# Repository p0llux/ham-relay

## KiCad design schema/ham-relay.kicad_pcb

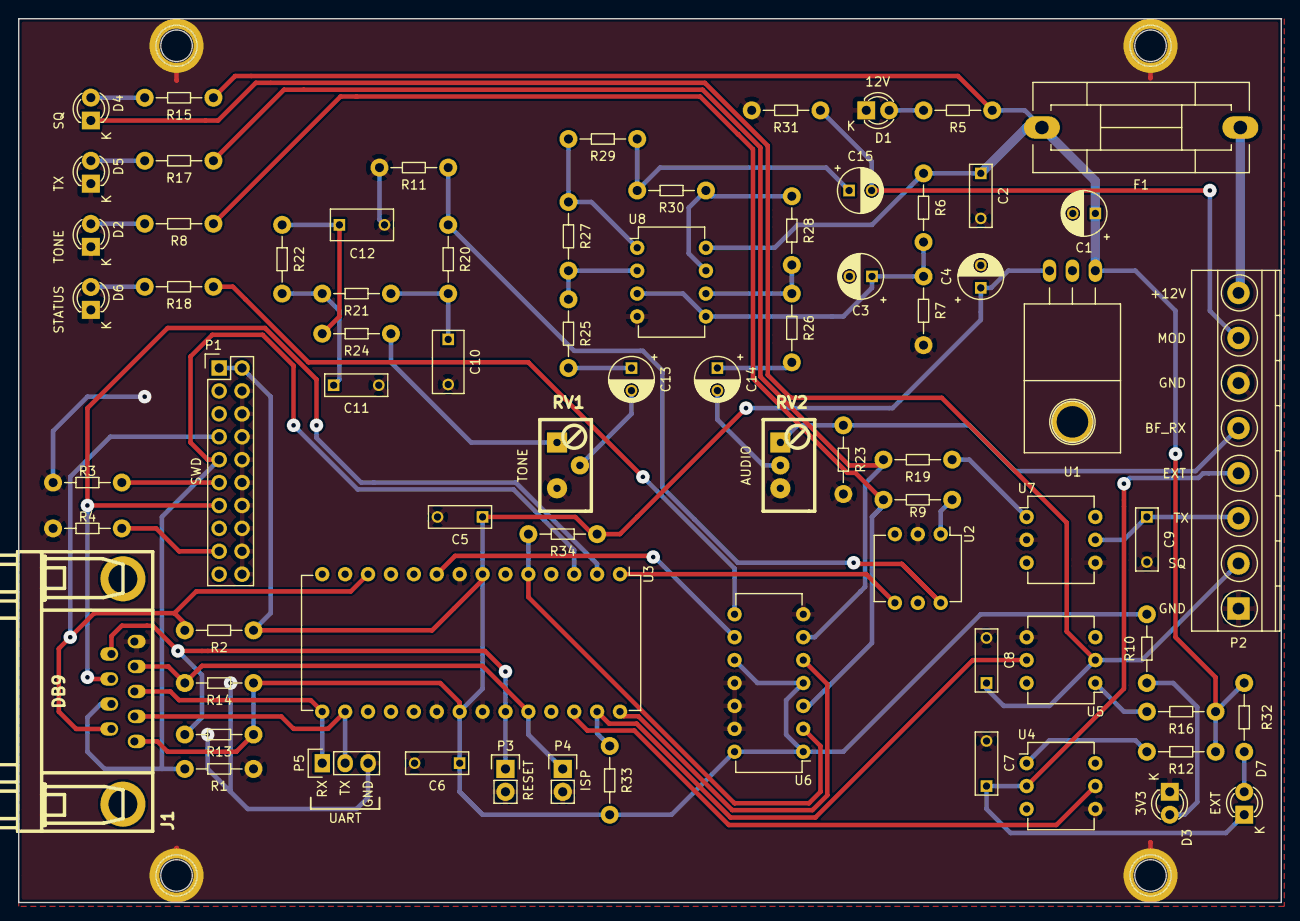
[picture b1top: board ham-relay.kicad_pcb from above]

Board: 2 copper layers, 140.0 x 98.0 mm, 78 parts (0 on the bottom side), 53 nets.

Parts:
C1, C3, C13, C14, C15: 10µF; C_Radial_D5_L11_P2.5
C2, C7, C8, C9: 10nF; C_Rect_L7_W2.5_P5
C4: 1µF; C_Radial_D5_L11_P2.5
C5, C6, C11: 100nF; C_Rect_L7_W2.5_P5
C10: 330nF; C_Rect_L7_W3.5_P5
C12: 33nF; C_Rect_L7_W3.5_P5
D1: 12V; LED-3MM
D2: TONE; LED-3MM
D3: 3V3; LED-3MM
D4: RX; LED-3MM
D5: TX; LED-3MM
D6: STATUS; LED-3MM
D7: EXT; LED-3MM
F1: FUSE; Fuseholder5x20_horiz_SemiClosed_Casing10x25mm
HOLE1, HOLE2, HOLE2#2, HOLE2#3, HOLE2#4: 1pin
J1: DB9; DB_9F
P1: JTAG; Pin_Header_Straight_2x10
P2: CONN_01X08; TerminalBlock_Pheonix_MKDS1.5-8pol
P3: RESET; Pin_Header_Straight_1x02
P4: ISP; Pin_Header_Straight_1x02
P5: CONN_01X03; Pin_Header_Straight_1x03
R1, R2, R3, R4, R13, R14: 10k; Resistor_Horizontal_RM08mm
R5: 1k; Resistor_Horizontal_RM08mm
R6, R7, R25, R26: 47k; Resistor_Horizontal_RM08mm
R8: 180; Resistor_Horizontal_RM08mm
R9, R19: 330; Resistor_Horizontal_RM08mm
R10, R20: 560; Resistor_Horizontal_RM08mm
R11: 2k2; Resistor_Horizontal_RM08mm
R12, R16: 2k7; Resistor_Horizontal_RM08mm
R15, R18, R21, R23, R31: 1k8; Resistor_Horizontal_RM08mm
R17: 270; Resistor_Horizontal_RM08mm
R22: 5k6; Resistor_Horizontal_RM08mm
R24: 22k; Resistor_Horizontal_RM08mm
R27: 680k; Resistor_Horizontal_RM08mm
R28: 330k; Resistor_Horizontal_RM08mm
R29, R30: 1k2; Resistor_Horizontal_RM08mm
R32: 15k; Resistor_Horizontal_RM08mm
R33, R34: 56k; Resistor_Horizontal_RM08mm
RV1: 10k; POT93YB
RV2: 1k; POT93YA
U1: REG3V3; TO-220_Neutral123_Horizontal
U2: LH1540; DIP-6_W7.62mm
U3: LPC1114FN28/102; DIP-28_W15.24mm
U4, U5, U7: MCA231; DIP-6_W7.62mm
U6: 74HC126N; DIP-14_W7.62mm
U8: TBB1458; DIP-8_W7.62mm

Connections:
+3V3: C4.1, C5.1, C6.1, J1.1, P1.1, P1.2, R2.1, R10.1, R13.1, R14.1, R33.1, R34.1, U3.7, U3.21, U6.1, U6.4, U6.10, U6.14
+12V: F1.1, P2.8
/Audio/AUDIO_IN: P2.5, R23.1, RV2.1
/Audio/AUDIO_OUT: C15.2, P2.7, R31.1
/Audio/TONE: R11.1, R20.2, U2.6
/EXT: U3.26, U4.5
/EXT_CR: C7.1, D7.1, P2.4, U4.2
/ISP: J1.4, P4.1, R14.2, U3.24
/RESET: J1.9, P3.1, R13.2, U3.23
/RX: J1.3, P5.1, U3.15
/RXE: R33.2, U3.27, U5.5
/RX_CR: C8.1, D4.1, P2.2, U5.2
/SWCLK: J1.7, P1.9, R1.1, U3.3
/SWDIO: J1.6, P1.7, R2.2, U3.12
/SWO: J1.8, P1.13, U3.2
/TONE: U2.4, U3.1
/TONE_SW: R8.1, R9.1, U6.3
/TX: J1.2, P5.2, U3.16
/TXE: R17.1, R19.1, U6.6
/TX_CR: C9.1, P2.3, U7.5
GND: C1.2, C2.2, C3.2, C4.2, C5.2, C6.2, C7.2, C8.2, C9.2, C10.2, C11.2, C12.2, D1.1, D2.1, D3.1, D5.1, D6.1, HOLE1.1, HOLE2.1, HOLE2#2.1, HOLE2#3.1, HOLE2#4.1, J1.5, P1.4, P1.6, P1.8, P1.10, P1.12, P1.14, P1.16, P1.18, P1.20, P2.1, P2.6, P3.2, P4.2, P5.3, R1.2, R3.2, R4.2, R7.2, R11.2, R23.2, R31.2, RV1.3, RV2.3, U2.2, U3.8, U3.20, U3.22, U4.4, U5.4, U6.7, U6.11, U6.12, U6.13, U7.2, U7.4, U8.4
unnamed: C10.1, R20.1, R21.2
unnamed: C11.1, R21.1, R22.2
unnamed: C12.1, R22.1, R24.2
unnamed: C13.1, R25.1
unnamed: C13.2, RV1.2
unnamed: C14.1, R26.1
unnamed: C14.2, RV2.2
unnamed: C15.1, R29.2, R30.2
unnamed: D1.2, R5.2
unnamed: D2.2, R8.2
unnamed: D3.2, R10.2
unnamed: D4.2, R15.2
unnamed: D5.2, R17.2
unnamed: D6.2, R18.2
unnamed: D7.2, R32.2
unnamed: P1.11, R3.1
unnamed: P1.17, R4.1
unnamed: R9.2, U2.1
unnamed: R12.2, U4.1
unnamed: R16.2, U5.1
unnamed: R18.1, U6.8
unnamed: R19.2, U7.1
unnamed: R24.1, RV1.1
unnamed: R25.2, R27.1, U8.2
unnamed: R26.2, R28.1, U8.6
unnamed: R27.2, R29.1, U8.1
unnamed: R28.2, R30.1, U8.7
unnamed: R34.2, U3.5, U6.2
unnamed: U3.9, U6.9
unnamed: U3.28, U6.5
VCC: C1.1, C2.1, F1.2, R5.1, R6.1, R12.1, R15.1, R16.1, R32.1, U8.8
VCC/2: C3.1, R6.2, R7.1, U8.3, U8.5

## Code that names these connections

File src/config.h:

#ifndef __HAVE_CONFIG_H
#define __HAVE_CONFIG_H

#define LED_STATUS_PIO     IOCON_PIO1_0
#define LED_STATUS_PORT    1
#define LED_STATUS_PIN     0
#define LED_INVERTED_LOGIC false

#define TXE_PIO      IOCON_PIO0_7
#define TXE_PORT     0
#define TXE_PIN      7
#define TXE_CONFIG   IOCON_MODE_INACT | IOCON_FUNC0

#define RXE_PIO      IOCON_PIO0_4
#define RXE_PORT     0
#define RXE_PIN      4
#define RXE_CONFIG   (IOCON_FUNC0)

#define EXT_PIO      IOCON_PIO0_3
#define EXT_PORT     0
#define EXT_PIN      3
#define EXT_CONFIG   (IOCON_FUNC0 | IOCON_MODE_PULLUP | IOCON_DIGMODE_EN)

#define TONE_PIO     IOCON_PIO0_8
#define TONE_PORT    0
#define TONE_PIN     8

#define TONE_SW_PIO  IOCON_PIO0_5
#define TONE_SW_PORT 0
#define TONE_SW_PIN  5

#define TX_READY_DELAY_MS 150

#define TONE_DEFAULT_HZ  900
#define TONE_EXT_HZ      440

#define MORSE_SHORT_DURATION_MS 80
#define MORSE_LONG_DURATION_MS  (MORSE_SHORT_DURATION_MS * 3)
#define MORSE_PAUSE_DURATION_MS (MORSE_SHORT_DURATION_MS * 3)
#define MORSE_SPACE_DURATION_MS (MORSE_SHORT_DURATION_MS * 7)

#define CALL_INTERVAL_SEC   300
#define CALL_DELAY_AFTER_TX  10
#define CALL_STRING         "ON0LBN"
#define CALL_POST_DELAY_MS  100

#define ROGER_BEEP_DELAY_MS    440
#define ROGER_BEEP_DURATION_MS 250

#define WDT_TIMEOUT_SEC        1000

#define STATUS_PATTERN_OK      0x00000003
#define STATUS_PATTERN_EXT     0x0000FFFF

#endif /* __HAVE_CONFIG_H */

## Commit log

2015-10-26 Add basic liblpc11 based on LPCOpen
2015-11-02 Add blink test code
2015-11-02 Add UART test code
2015-11-02 Add debug test code
2015-11-02 Add button test code
2015-11-02 Start working on firmware
2015-11-02 Add morse signal generator
2015-11-08 Fix openocd.sh
2015-11-22 Fix Morse generator
2015-11-22 Use button to start sending Morse ID
2015-12-07 Add KiCAD schematics
2015-12-13 * Rename I/O config names * Add support for TXE (tx.c)
2015-12-13 Rename mixer.[ch] into tone.[ch]
2015-12-13 Update schematics
2015-12-13 Add status LED on schematics
2015-12-23 First routing
2015-12-24 Update schematic
2015-12-25 More changes
2016-01-23 Update footprints
2016-02-14 Design rules
2016-02-14 Add EXT_CR support
2016-02-14 Component placement
2016-02-14 Routing
2016-02-14 * Add EXT LED * Silkscreen
2016-02-14 Missing net
2016-02-15 Improve routing for better ground plane and thermal relieved pads
2016-02-15 Only missing the holes
2016-02-15 Production ready
2016-03-28 Switch to 1ms systick
2016-03-28 Add code to send station ID at given interval
2016-03-28 Detect inputs
2016-03-28 Change tone on EXT, detect RXE
2016-03-28 Add support for roger beep
2016-04-09 Start fixing schematics
2016-04-10 Update schematics after prototype validation
2016-04-10 LED testing on proto board
2016-04-10 Have call_transmit_if_needed return whether it has sent the call or not
2016-04-10 Update config for real board
2016-04-10 We need to reduce the debug baudrate now that we are using the IRC
2016-04-10 Fix input interrupts
2016-04-10 Real PCB does not have a TONE_LED
2016-04-10 Use the internal IRC as reference clock
2016-04-10 Fix TX usage
2016-04-10 Enable watchdog
2016-04-10 Status LED
2016-04-10 Fix merge
2016-04-10 Completely revamp the way TX is set and kept on
2016-04-10 Validated version
